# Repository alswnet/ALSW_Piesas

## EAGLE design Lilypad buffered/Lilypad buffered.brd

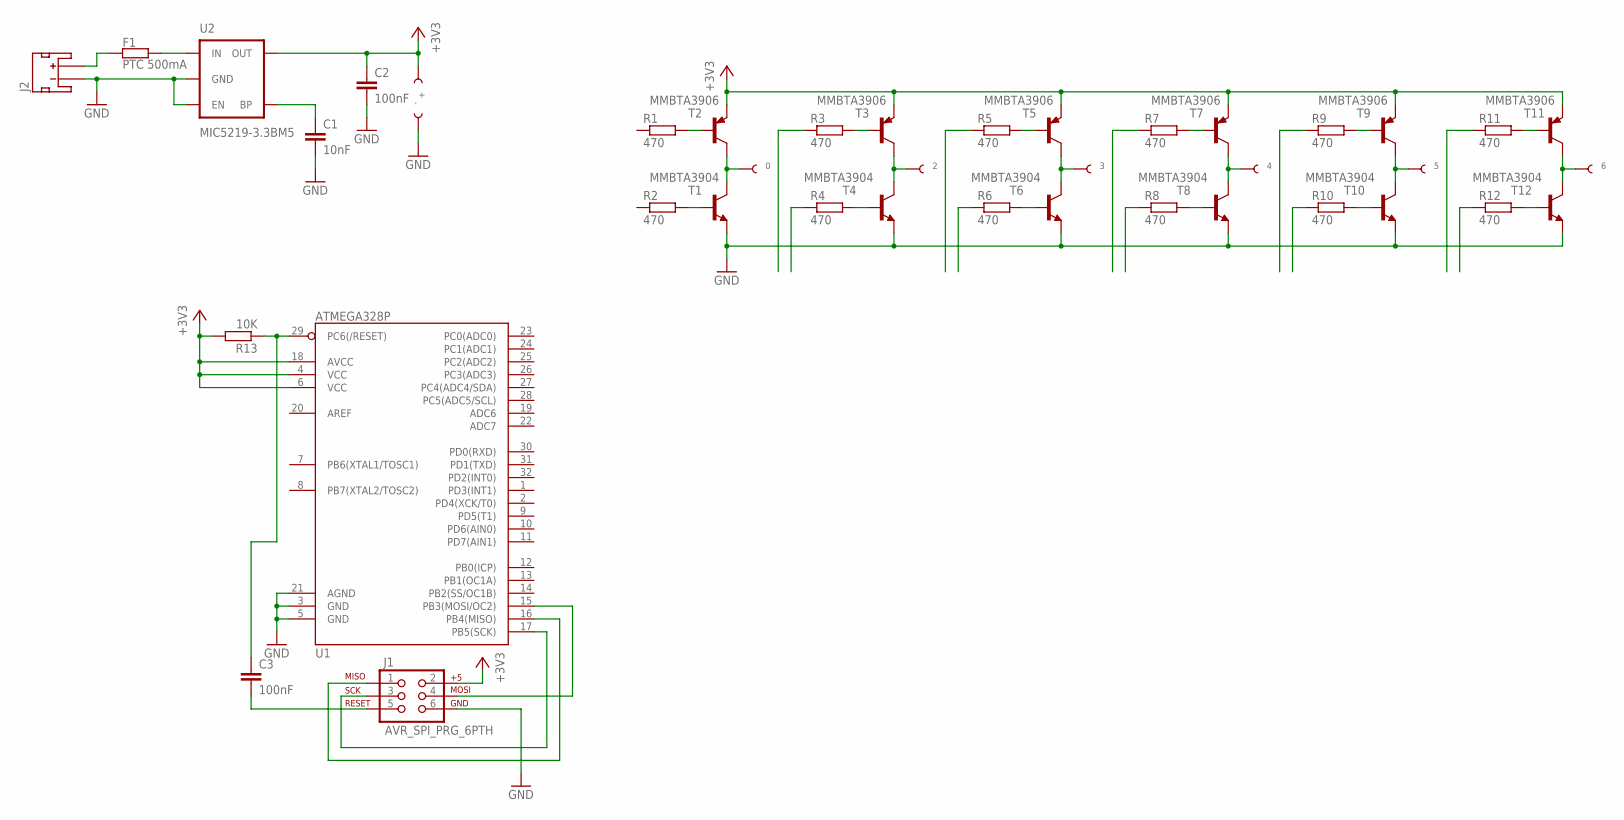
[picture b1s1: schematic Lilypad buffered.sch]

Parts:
C1: 10nF; C0805K
C2, C3: 100nF; C0805K
F1: PTC 500mA; SMD-2012
J1: AVR_SPI_PRG_6PTH; 2X3
J2: JST_2MM_MALE; JST-2-SMD
R1, R2, R3, R4, R5, R6, R7, R8, R9, R10, R11, R12: 470; R0603
R13: 10K; R0603
T1, T4, T6, T8, T10, T12: MMBTA3904; SOT23-BEC
T2, T3, T5, T7, T9, T11: MMBTA3906; SOT23-BEC
U1: ATMEGA328P; TQFP32-08
U2: MIC5219-3.3BM5; SOT23-5
U$1: 0; PETAL-LONG-1-2SIDE
U$2: 2; PETAL-LONG-1-2SIDE
U$3: 3; PETAL-LONG-1-2SIDE
U$4: 4; PETAL-LONG-1-2SIDE
U$5: 5; PETAL-LONG-1-2SIDE
U$6: 6; PETAL-LONG-1-2SIDE
U$9: +; PETAL-LONG-1-2SIDE
U$10: -; PETAL-LONG-1-2SIDE

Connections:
+3V3: C2.1, J1.2, R13.2, T2.E, T3.E, T5.E, T7.E, T9.E, T11.E, U1.4 (VCC), U1.6 (VCC), U1.18 (AVCC), U2.5 (OUT), U$9.1
GND: C1.2, C2.2, J1.6, J2.1 (-), T1.E, T4.E, T6.E, T8.E, T10.E, T12.E, U1.3 (GND), U1.5 (GND), U1.21 (AGND), U2.2 (GND), U2.3 (EN), U$10.1
unnamed: T1.C, T2.C, U$1.1
unnamed: R1.2, T2.B
unnamed: R2.2, T1.B
unnamed: R4.2, T4.B
unnamed: R3.2, T3.B
unnamed: T3.C, T4.C, U$2.1
unnamed: R6.2, T6.B
unnamed: R5.2, T5.B
unnamed: T5.C, T6.C, U$3.1
unnamed: R8.2, T8.B
unnamed: R7.2, T7.B
unnamed: T7.C, T8.C, U$4.1
unnamed: R10.2, T10.B
unnamed: R9.2, T9.B
unnamed: T9.C, T10.C, U$5.1
unnamed: R12.2, T12.B
unnamed: R11.2, T11.B
unnamed: T11.C, T12.C, U$6.1
unnamed: C1.1, U2.4 (BP)
unnamed: F1.P$2, J2.2 (+)
unnamed: J1.3, U1.17 (PB5(SCK))
unnamed: J1.1, U1.16 (PB4(MISO))
unnamed: J1.4, U1.15 (PB3(MOSI/OC2))
unnamed: C3.1, R13.1, U1.29 (PC6(/RESET))
unnamed: F1.P$1, U2.1 (IN)
unnamed: C3.2, J1.5

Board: 2 copper layers, 41 parts (0 on the bottom side), 28 nets, no tracks yet.

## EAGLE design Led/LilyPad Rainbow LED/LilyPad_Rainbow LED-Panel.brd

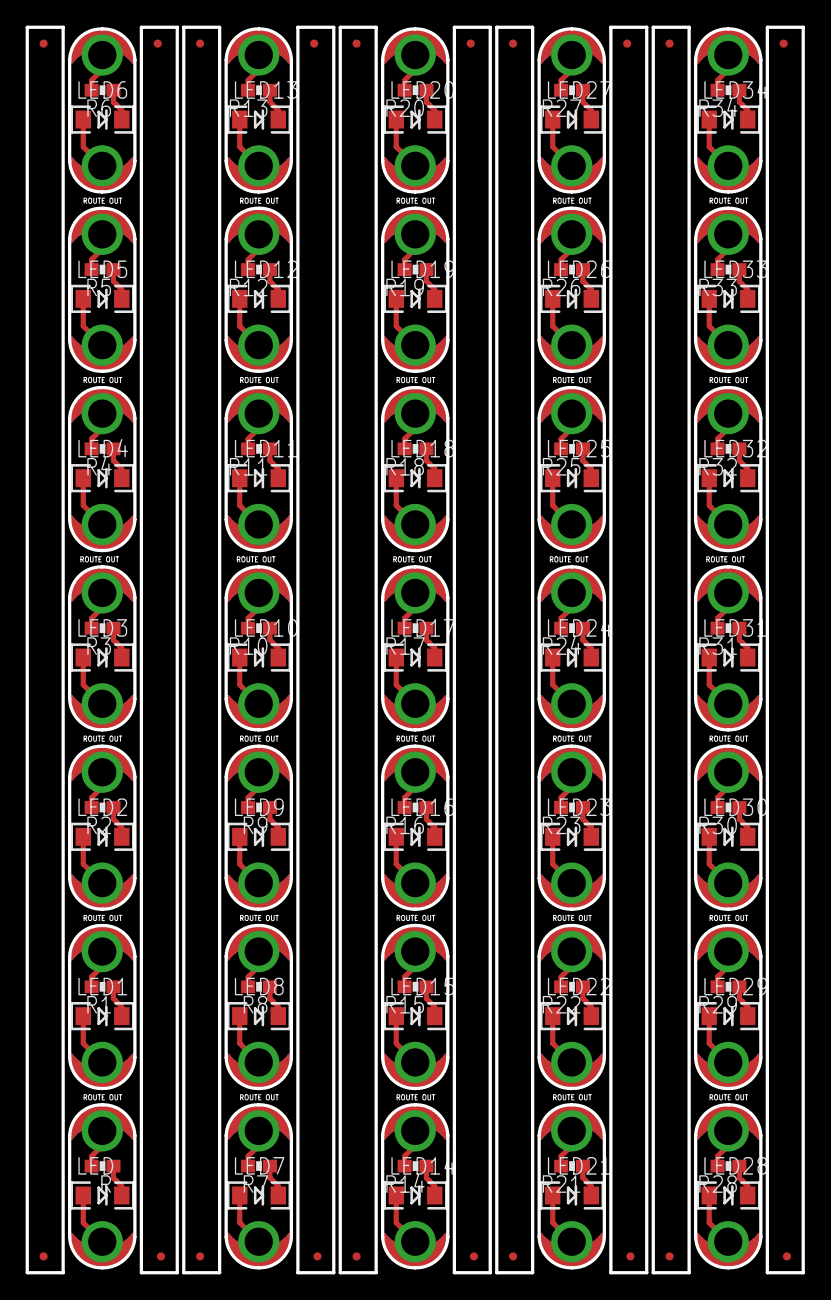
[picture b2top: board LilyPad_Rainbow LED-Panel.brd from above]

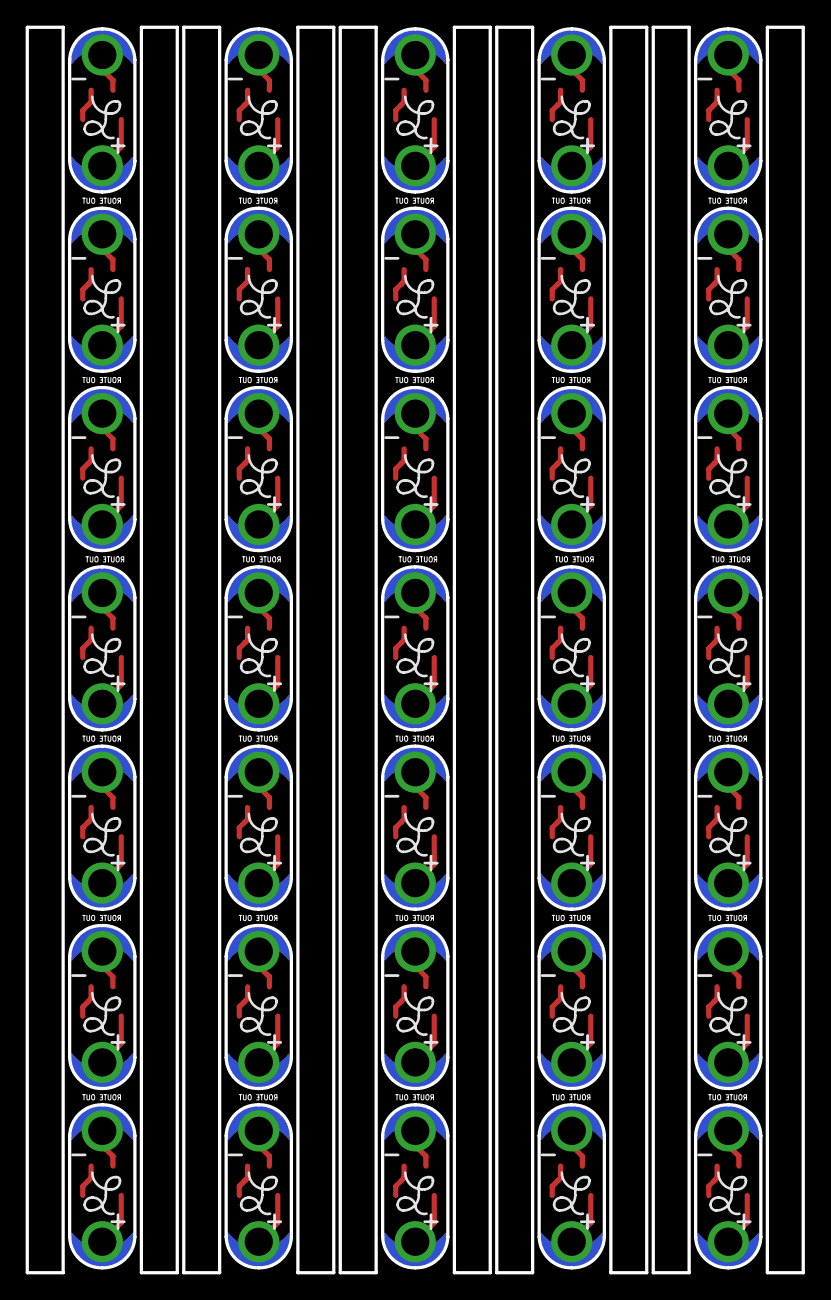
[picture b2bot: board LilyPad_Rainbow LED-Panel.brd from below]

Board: 2 copper layers, 60.5 x 97.0 mm, 195 parts (35 on the bottom side), 105 nets.

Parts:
E$1, E$2, E$3, E$4, E$5, E$6, E$7, E$8, E$9, E$10, E$11, E$12, E$13, E$14, E$15, E$16, E$17, E$18, E$19, E$20: MICRO-FIDUCIAL
LED, LED1, LED2, LED3, LED4, LED5, LED6, LED7, LED8, LED9, LED10, LED11, LED12, LED13, LED14, LED15, LED16, LED17, LED18, LED19, LED20, LED21, LED22, LED23, LED24, LED25, LED26, LED27, LED28, LED29, LED30, LED31, LED32, LED33, LED34: White; LED-1206
LED+, LED+1, LED+2, LED+3, LED+4, LED+5, LED+6, LED+7, LED+8, LED+9, LED+10, LED+11, LED+12, LED+13, LED+14, LED+15, LED+16, LED+17, LED+18, LED+19, LED+20, LED+21, LED+22, LED+23, LED+24, LED+25, LED+26, LED+27, LED+28, LED+29, LED+30, LED+31, LED+32, LED+33, LED+34: SEWTAP6; PETAL-SMALL
LED-, LED-1, LED-2, LED-3, LED-4, LED-5, LED-6, LED-7, LED-8, LED-9, LED-10, LED-11, LED-12, LED-13, LED-14, LED-15, LED-16, LED-17, LED-18, LED-19, LED-20, LED-21, LED-22, LED-23, LED-24, LED-25, LED-26, LED-27, LED-28, LED-29, LED-30, LED-31, LED-32, LED-33, LED-34: SEWTAP6; PETAL-SMALL
LOGO1, LOGO2, LOGO3, LOGO4, LOGO5, LOGO6, LOGO7, LOGO8, LOGO9, LOGO10, LOGO11, LOGO12, LOGO13, LOGO14, LOGO15, LOGO16, LOGO17, LOGO18, LOGO19, LOGO20, LOGO21, LOGO22, LOGO23, LOGO24, LOGO25, LOGO26, LOGO27, LOGO28, LOGO29, LOGO30, LOGO31, LOGO32, LOGO33, LOGO34, LOGO35: LOGO-LPL; LOGO-L
R, R1, R2, R3, R4, R5, R6, R7, R8, R9, R10, R11, R12, R13, R14, R15, R16, R17, R18, R19, R20, R21, R22, R23, R24, R25, R26, R27, R28, R29, R30, R31, R32, R33, R34: 100; 0603-RES

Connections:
+: LED.A, LED+.1
+1: LED1.A, LED+1.1
+2: LED2.A, LED+2.1
+3: LED3.A, LED+3.1
+4: LED4.A, LED+4.1
+5: LED5.A, LED+5.1
+6: LED6.A, LED+6.1
+7: LED7.A, LED+7.1
+8: LED8.A, LED+8.1
+9: LED9.A, LED+9.1
+10: LED10.A, LED+10.1
+11: LED11.A, LED+11.1
+12: LED12.A, LED+12.1
+13: LED13.A, LED+13.1
+14: LED14.A, LED+14.1
+15: LED15.A, LED+15.1
+16: LED16.A, LED+16.1
+17: LED17.A, LED+17.1
+18: LED18.A, LED+18.1
+19: LED19.A, LED+19.1
+20: LED20.A, LED+20.1
+21: LED21.A, LED+21.1
+22: LED22.A, LED+22.1
+23: LED23.A, LED+23.1
+24: LED24.A, LED+24.1
+25: LED25.A, LED+25.1
+26: LED26.A, LED+26.1
+27: LED27.A, LED+27.1
+28: LED28.A, LED+28.1
+29: LED29.A, LED+29.1
+30: LED30.A, LED+30.1
+31: LED31.A, LED+31.1
+32: LED32.A, LED+32.1
+33: LED33.A, LED+33.1
+34: LED34.A, LED+34.1
-: LED-.1, R.2
-1: LED-1.1, R1.2
-2: LED-2.1, R2.2
-3: LED-3.1, R3.2
-4: LED-4.1, R4.2
-5: LED-5.1, R5.2
-6: LED-6.1, R6.2
-7: LED-7.1, R7.2
-8: LED-8.1, R8.2
-9: LED-9.1, R9.2
-10: LED-10.1, R10.2
-11: LED-11.1, R11.2
-12: LED-12.1, R12.2
-13: LED-13.1, R13.2
-14: LED-14.1, R14.2
-15: LED-15.1, R15.2
-16: LED-16.1, R16.2
-17: LED-17.1, R17.2
-18: LED-18.1, R18.2
-19: LED-19.1, R19.2
-20: LED-20.1, R20.2
-21: LED-21.1, R21.2
-22: LED-22.1, R22.2
-23: LED-23.1, R23.2
-24: LED-24.1, R24.2
-25: LED-25.1, R25.2
-26: LED-26.1, R26.2
-27: LED-27.1, R27.2
-28: LED-28.1, R28.2
-29: LED-29.1, R29.2
-30: LED-30.1, R30.2
-31: LED-31.1, R31.2
-32: LED-32.1, R32.2
-33: LED-33.1, R33.2
-34: LED-34.1, R34.2
unnamed: LED.C, R.1
unnamed: LED1.C, R1.1
unnamed: LED2.C, R2.1
unnamed: LED3.C, R3.1
unnamed: LED4.C, R4.1
unnamed: LED5.C, R5.1
unnamed: LED6.C, R6.1
unnamed: LED7.C, R7.1
unnamed: LED8.C, R8.1
unnamed: LED9.C, R9.1
unnamed: LED10.C, R10.1
unnamed: LED11.C, R11.1
unnamed: LED12.C, R12.1
unnamed: LED13.C, R13.1
unnamed: LED14.C, R14.1
unnamed: LED15.C, R15.1
unnamed: LED16.C, R16.1
unnamed: LED17.C, R17.1
unnamed: LED18.C, R18.1
unnamed: LED19.C, R19.1
unnamed: LED20.C, R20.1
unnamed: LED21.C, R21.1
unnamed: LED22.C, R22.1
unnamed: LED23.C, R23.1
unnamed: LED24.C, R24.1
unnamed: LED25.C, R25.1
unnamed: LED26.C, R26.1
unnamed: LED27.C, R27.1
unnamed: LED28.C, R28.1
unnamed: LED29.C, R29.1
unnamed: LED30.C, R30.1
unnamed: LED31.C, R31.1
unnamed: LED32.C, R32.1
unnamed: LED33.C, R33.1
unnamed: LED34.C, R34.1

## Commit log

2013-09-19 Iniciando el repo con las cosas de sparfun
2013-09-19 Los gerber hechos en joksan para la producion de led
2013-09-23 Agregados los archivos de eagle para la tarjeta de lilypad con bufferes para chalieplexing
2013-09-26 Cambiado el formato de las perforaciones de Excellon a gerber-RS274X. - Actualizados los gerber involucrados. - Actualizado archivo cam involucrado. - Mejoras menores a la tarjeta de Lilypad con buff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
2013-10-17 Continuado el trabajo sobre el esquematico. Terminado sistema minimo y fuente de suministro (con proteccion).

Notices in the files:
parts and their libraries:
SparkFun-Aesthetics: Licensing: CC v3.0 Share-Alike You are welcome to use this library for commercial purposes.
